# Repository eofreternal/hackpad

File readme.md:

This is my hackpad!

My hackpad has 4 keys in the WASD layout (with one key in the first row and 3 keys in the second row) and a rotary encoder. It uses KMK for its firmware.

I designed this by following [Hackpad](https://hackpad.hackclub.com) and took inspiration from [Orpheuspad](https://github.com/qcoral/orpheuspad)

# Features

4 Cherry MX-style keys
A EC11 rotary encoder for volume (or whatever else you'd like)

# BOM

- 1x PCB
- 1x case
- 4x Cherry MX-style switches
- 1x EC11 Rotary Encoder
- 6x DSA keycaps
- 1x XIAO RP2040
- 4x M3x16mm screws
- 4x M3x5mx4mm heatset inserts

# Schematic

# PCB

# Case

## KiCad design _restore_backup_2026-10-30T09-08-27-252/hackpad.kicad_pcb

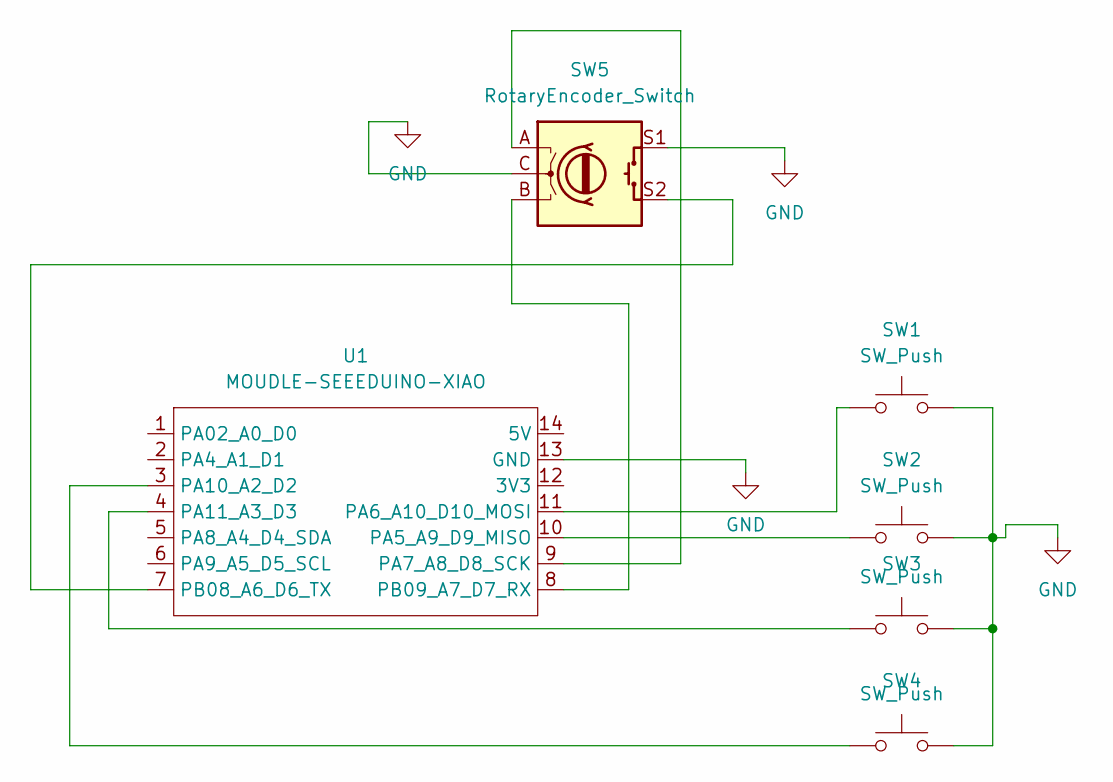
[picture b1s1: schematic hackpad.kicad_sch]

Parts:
SW1, SW2, SW3, SW4: SW_Push; SW_Cherry_MX_1.00u_PCB
SW5: RotaryEncoder_Switch; RotaryEncoder_Alps_EC11E-Switch_Vertical_H20mm
U1: MOUDLE-SEEEDUINO-XIAO; XIAO-Generic-Hybrid-14P-2.54-21X17.8MM

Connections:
GND: SW1.2, SW2.2, SW3.2, SW4.2, SW5.C, SW5.S1, U1.13 (GND)
unnamed: SW2.1, U1.10 (PA5_A9_D9_MISO)
unnamed: SW1.1, U1.11 (PA6_A10_D10_MOSI)
unnamed: SW5.A, U1.9 (PA7_A8_D8_SCK)
unnamed: SW4.1, U1.3 (PA10_A2_D2)
unnamed: SW3.1, U1.4 (PA11_A3_D3)
unnamed: SW5.S2, U1.7 (PB08_A6_D6_TX)
unnamed: SW5.B, U1.8 (PB09_A7_D7_RX)

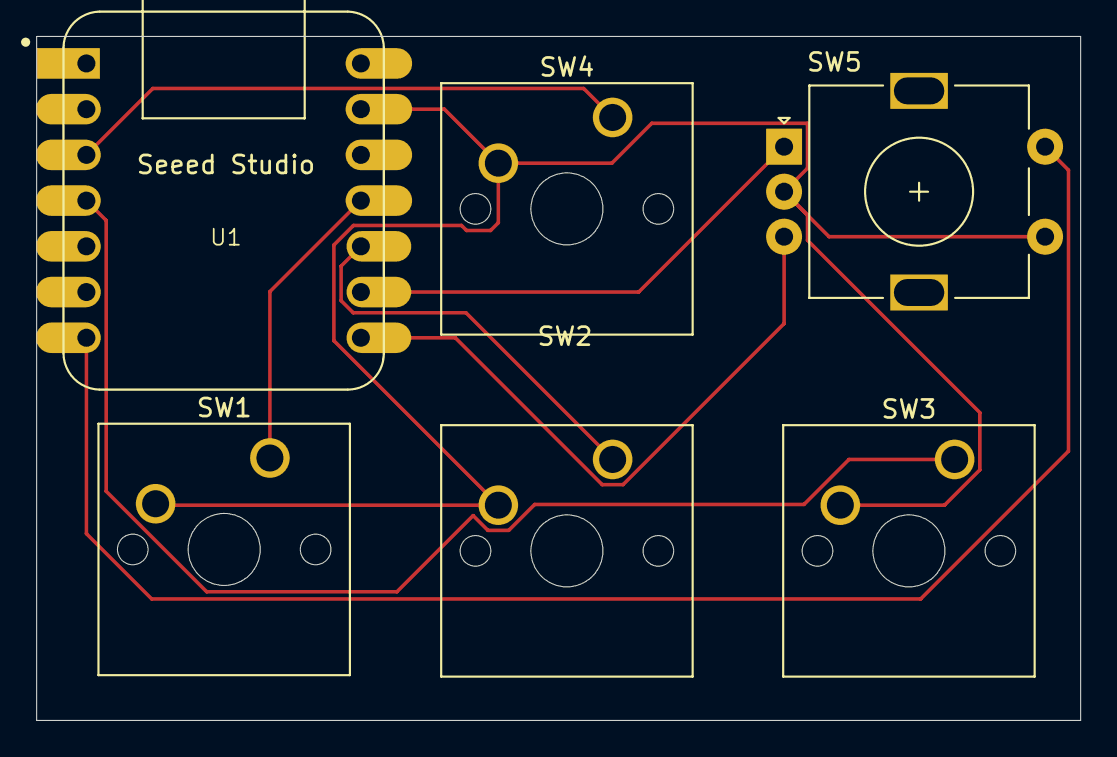
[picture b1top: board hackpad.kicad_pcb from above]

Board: 2 copper layers, 58.0 x 38.0 mm, 6 parts (0 on the bottom side), 8 nets.
